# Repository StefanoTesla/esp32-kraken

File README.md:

# esp32 Kraken
A funny name for a simple pcb for a esp32 prototipe, designed to use all i/o as input and output with different configurations

This board is deisgned to imporve the quality of development forgetting the protobard with folating wires and no-contact noise.

The pcb is designed by eagle

The size of the board is 100x100mm perfect to pass as prototype in jlcpb and get it at a low price (around 22$ for 5 boards).

Currently the pcb is designed to fit with esp32 dev kit with 30pins

The pcb.zip file contain the geber file to upload in your favourite pcb manufacturing site ♥️

## How does it work?

Very well! 🙂 with this configuration you don't have limit, all I/O are ready to use in all the way you can think let's take a look:

### Power supply

If you want you can add a LM2596 DC-DC step down, otherwise you can give 5V directly on OUT+ and OUT-

In the right side there's some 5V spare pins where you can pluc i2c devices or what you want

### V voltage selector
As you can see there's a GND and a V pin for each input, you can choose the V voltage as you prefer in 5V or 3.3V bridgin one of the the selector in the buttom, or give your own voltage to the V line (this will help cause 3.3V are providev from internal esp32 voltage regulator

### Input

Free to choose in wich way you wanna use it, in the past I hade some problem using internal pull up/pull down resistor and this is why I build this board in a first step.

You can provide olso 5V signal to the esp32 adding a zener diode, or a fancy 10K resistor but after don't cry if your esp32 blow up 🤯 furthermore the ground of all two system shuold be connected between

#### External Pull Up/Down Resistor

Pull down:

Pull Up

#### Directly input

You can give olso direct input of coure in two way, the white one, is more boring, you need a bridge but can be useful if you neet to measure the volatage, for the listless there's olso the red one solution

#### Others funny thing you can do

You can use a zener with resistor for limit the voltage, you can use a capacitor with a resistor for having an external debounce system, but be careful adding a lot of thing or your board become a christmas tree 🎄

### Output

Output can be use in three differt way, directly like the input with the same method, you can usa a bridge to measuere the voltage (yellow way) or plug the wire directly before gpio resistance (white way) , if you wanna plug a led you can simply add a resistor in the appropriate space (red way)

### Board notes

If you are not myopic you can see an I or an S near some GPIO, what they mean???

I stand for Only-Input GPIO

S stand for "Safety" that is you can use that output without going to have problems like pwm at the boot

## Hope you like it!

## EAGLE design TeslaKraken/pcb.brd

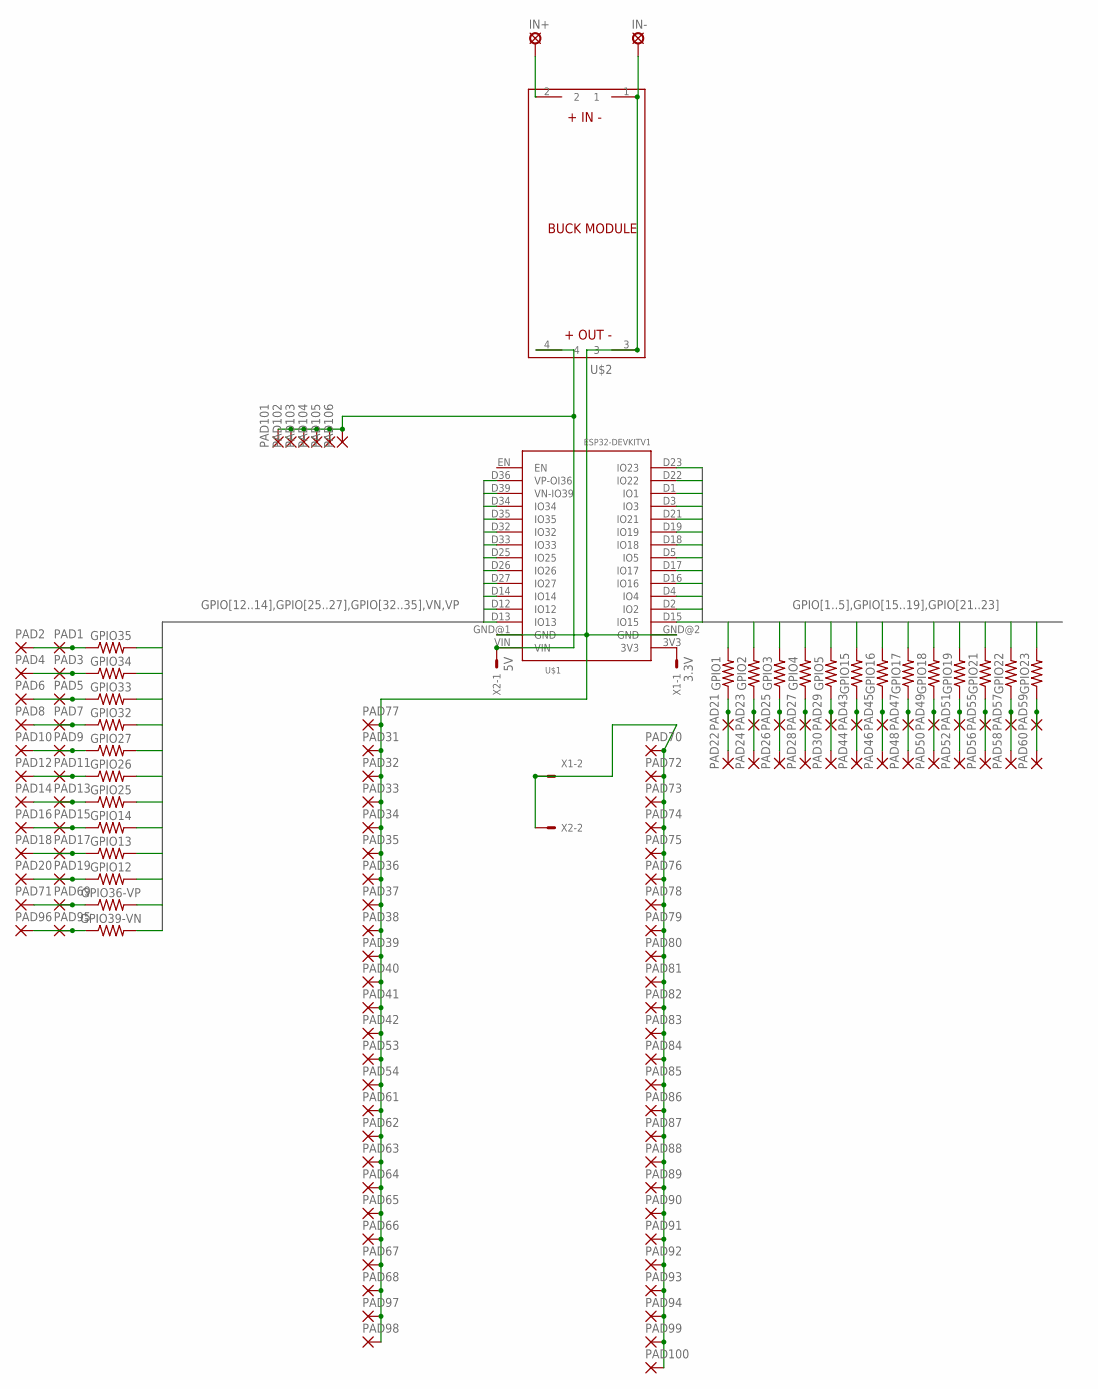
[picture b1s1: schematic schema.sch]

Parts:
GPIO1, GPIO2, GPIO3, GPIO4, GPIO5, GPIO12, GPIO13, GPIO14, GPIO15, GPIO16, GPIO17, GPIO18, GPIO19, GPIO21, GPIO22, GPIO23, GPIO25, GPIO26, GPIO27, GPIO32, GPIO33, GPIO34, GPIO35, GPIO36-VP, GPIO39-VN: AXIAL-0.3-KIT
IN+: SE14
IN-: SE14
PAD1, PAD2, PAD3, PAD4, PAD5, PAD6, PAD7, PAD8, PAD9, PAD10, PAD11, PAD12, PAD13, PAD14, PAD15, PAD16, PAD17, PAD18, PAD19, PAD20, PAD21, PAD22, PAD23, PAD24, PAD25, PAD26, PAD27, PAD28, PAD29, PAD30, PAD31, PAD32, PAD33, PAD34, PAD35, PAD36, PAD37, PAD38, PAD39, PAD40, PAD41, PAD42, PAD43, PAD44, PAD45, PAD46, PAD47, PAD48, PAD49, PAD50, PAD51, PAD52, PAD53, PAD54, PAD55, PAD56, PAD57, PAD58, PAD59, PAD60, PAD61, PAD62, PAD63, PAD64, PAD65, PAD66, PAD67, PAD68, PAD69, PAD70, PAD71, PAD72, PAD73, PAD74, PAD75, PAD76, PAD77, PAD78, PAD79, PAD80, PAD81, PAD82, PAD83, PAD84, PAD85, PAD86, PAD87, PAD88, PAD89, PAD90, PAD91, PAD92, PAD93, PAD94, PAD95, PAD96, PAD97, PAD98, PAD99, PAD100, PAD101, PAD102, PAD103, PAD104, PAD105, PAD106: 2,54/1,1
U$1: ESP32DEVKITV1; ESP32-DEVKITV1
U$2: BUCK_MODULEWITH_SMDPADS&THROUGHHOLES; BUCK_MODULE
X1: 3.3V; 22-23-2021
X2: 5V; 22-23-2021

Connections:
GPIO1: GPIO1.P$2 (2), U$1.D1 (IO1)
GPIO2: GPIO2.P$2 (2), U$1.D2 (IO2)
GPIO3: GPIO3.P$2 (2), U$1.D3 (IO3)
GPIO4: GPIO4.P$2 (2), U$1.D4 (IO4)
GPIO5: GPIO5.P$2 (2), U$1.D5 (IO5)
GPIO12: GPIO12.P$2 (2), U$1.D12 (IO12)
GPIO13: GPIO13.P$2 (2), U$1.D13 (IO13)
GPIO14: GPIO14.P$2 (2), U$1.D14 (IO14)
GPIO15: GPIO15.P$2 (2), U$1.D15 (IO15)
GPIO16: GPIO16.P$2 (2), U$1.D16 (IO16)
GPIO17: GPIO17.P$2 (2), U$1.D17 (IO17)
GPIO18: GPIO18.P$2 (2), U$1.D18 (IO18)
GPIO19: GPIO19.P$2 (2), U$1.D19 (IO19)
GPIO21: GPIO21.P$2 (2), U$1.D21 (IO21)
GPIO22: GPIO22.P$2 (2), U$1.D22 (IO22)
GPIO23: GPIO23.P$2 (2), U$1.D23 (IO23)
GPIO25: GPIO25.P$2 (2), U$1.D25 (IO25)
GPIO26: GPIO26.P$2 (2), U$1.D26 (IO26)
GPIO27: GPIO27.P$2 (2), U$1.D27 (IO27)
GPIO32: GPIO32.P$2 (2), U$1.D32 (IO32)
GPIO33: GPIO33.P$2 (2), U$1.D33 (IO33)
GPIO34: GPIO34.P$2 (2), U$1.D34 (IO34)
GPIO35: GPIO35.P$2 (2), U$1.D35 (IO35)
unnamed: GPIO35.P$1 (1), PAD1.1, PAD2.1
unnamed: GPIO34.P$1 (1), PAD3.1, PAD4.1
unnamed: GPIO33.P$1 (1), PAD5.1, PAD6.1
unnamed: GPIO32.P$1 (1), PAD7.1, PAD8.1
unnamed: GPIO27.P$1 (1), PAD9.1, PAD10.1
unnamed: GPIO26.P$1 (1), PAD11.1, PAD12.1
unnamed: GPIO25.P$1 (1), PAD13.1, PAD14.1
unnamed: GPIO14.P$1 (1), PAD15.1, PAD16.1
unnamed: GPIO13.P$1 (1), PAD17.1, PAD18.1
unnamed: GPIO12.P$1 (1), PAD19.1, PAD20.1
unnamed: GPIO1.P$1 (1), PAD21.1, PAD22.1
unnamed: GPIO2.P$1 (1), PAD23.1, PAD24.1
unnamed: GPIO3.P$1 (1), PAD25.1, PAD26.1
unnamed: GPIO4.P$1 (1), PAD27.1, PAD28.1
unnamed: GPIO5.P$1 (1), PAD29.1, PAD30.1
unnamed: PAD101.1, PAD102.1, PAD103.1, PAD104.1, PAD105.1, PAD106.1, U$1.VIN, U$2.4, X2.1
unnamed: IN-.MP, PAD31.1, PAD32.1, PAD33.1, PAD34.1, PAD35.1, PAD36.1, PAD37.1, PAD38.1, PAD39.1, PAD40.1, PAD41.1, PAD42.1, PAD53.1, PAD54.1, PAD61.1, PAD62.1, PAD63.1, PAD64.1, PAD65.1, PAD66.1, PAD67.1, PAD68.1, PAD77.1, PAD97.1, PAD98.1, U$1.GND@1 (GND), U$1.GND@2 (GND), U$2.1, U$2.3
unnamed: IN+.MP, U$2.2
unnamed: GPIO36-VP.P$1 (1), PAD69.1, PAD71.1
unnamed: PAD70.1, PAD72.1, PAD73.1, PAD74.1, PAD75.1, PAD76.1, PAD78.1, PAD79.1, PAD80.1, PAD81.1, PAD82.1, PAD83.1, PAD84.1, PAD85.1, PAD86.1, PAD87.1, PAD88.1, PAD89.1, PAD90.1, PAD91.1, PAD92.1, PAD93.1, PAD94.1, PAD99.1, PAD100.1, X1.2, X2.2
unnamed: GPIO39-VN.P$1 (1), PAD95.1, PAD96.1
unnamed: GPIO15.P$1 (1), PAD43.1, PAD44.1
unnamed: GPIO16.P$1 (1), PAD45.1, PAD46.1
unnamed: GPIO17.P$1 (1), PAD47.1, PAD48.1
unnamed: GPIO18.P$1 (1), PAD49.1, PAD50.1
unnamed: GPIO19.P$1 (1), PAD51.1, PAD52.1
unnamed: U$1.3V3, X1.1
unnamed: GPIO21.P$1 (1), PAD55.1, PAD56.1
unnamed: GPIO22.P$1 (1), PAD57.1, PAD58.1
unnamed: GPIO23.P$1 (1), PAD59.1, PAD60.1
VN: GPIO39-VN.P$2 (2), U$1.D39 (VN-IO39)
VP: GPIO36-VP.P$2 (2), U$1.D36 (VP-OI36)

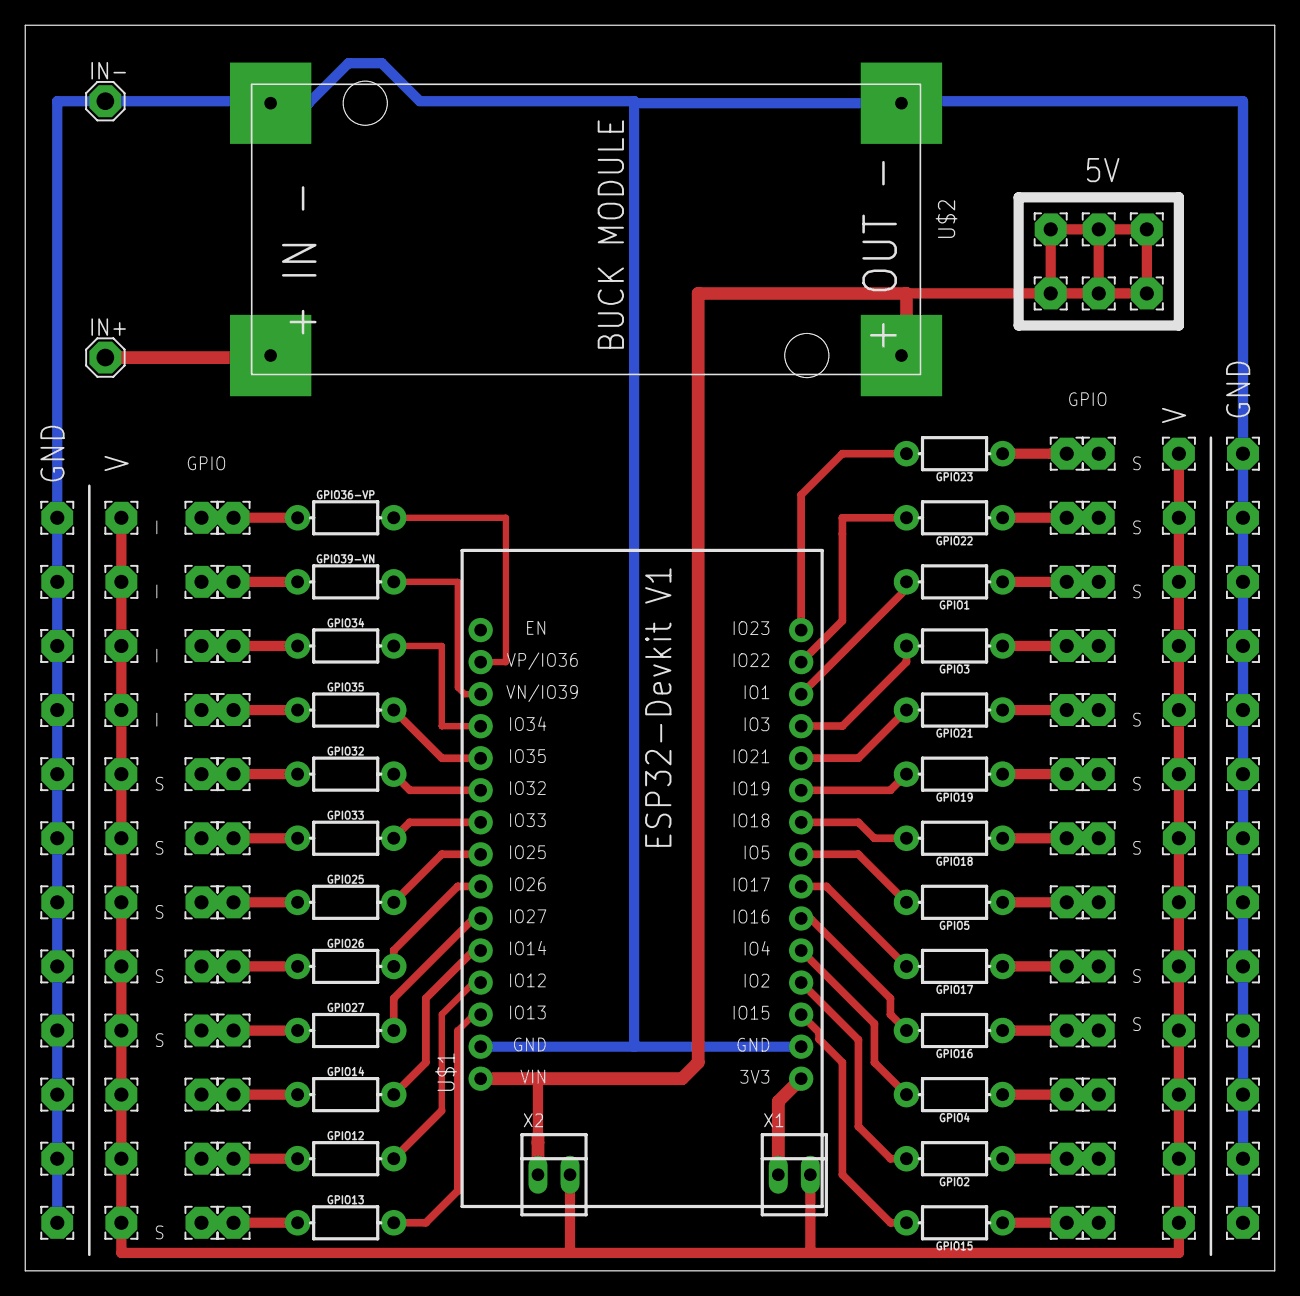
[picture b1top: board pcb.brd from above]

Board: 2 copper layers, 99.0 x 98.7 mm, 137 parts (0 on the bottom side), 55 nets.

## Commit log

2021-12-28 Eagle Project
2021-12-30 added images

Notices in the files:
parts and their libraries:
SparkFun-Resistors: Licensing: Creative Commons ShareAlike 4.0 International - https://creativecommons.org/licenses/by-sa/4.0
